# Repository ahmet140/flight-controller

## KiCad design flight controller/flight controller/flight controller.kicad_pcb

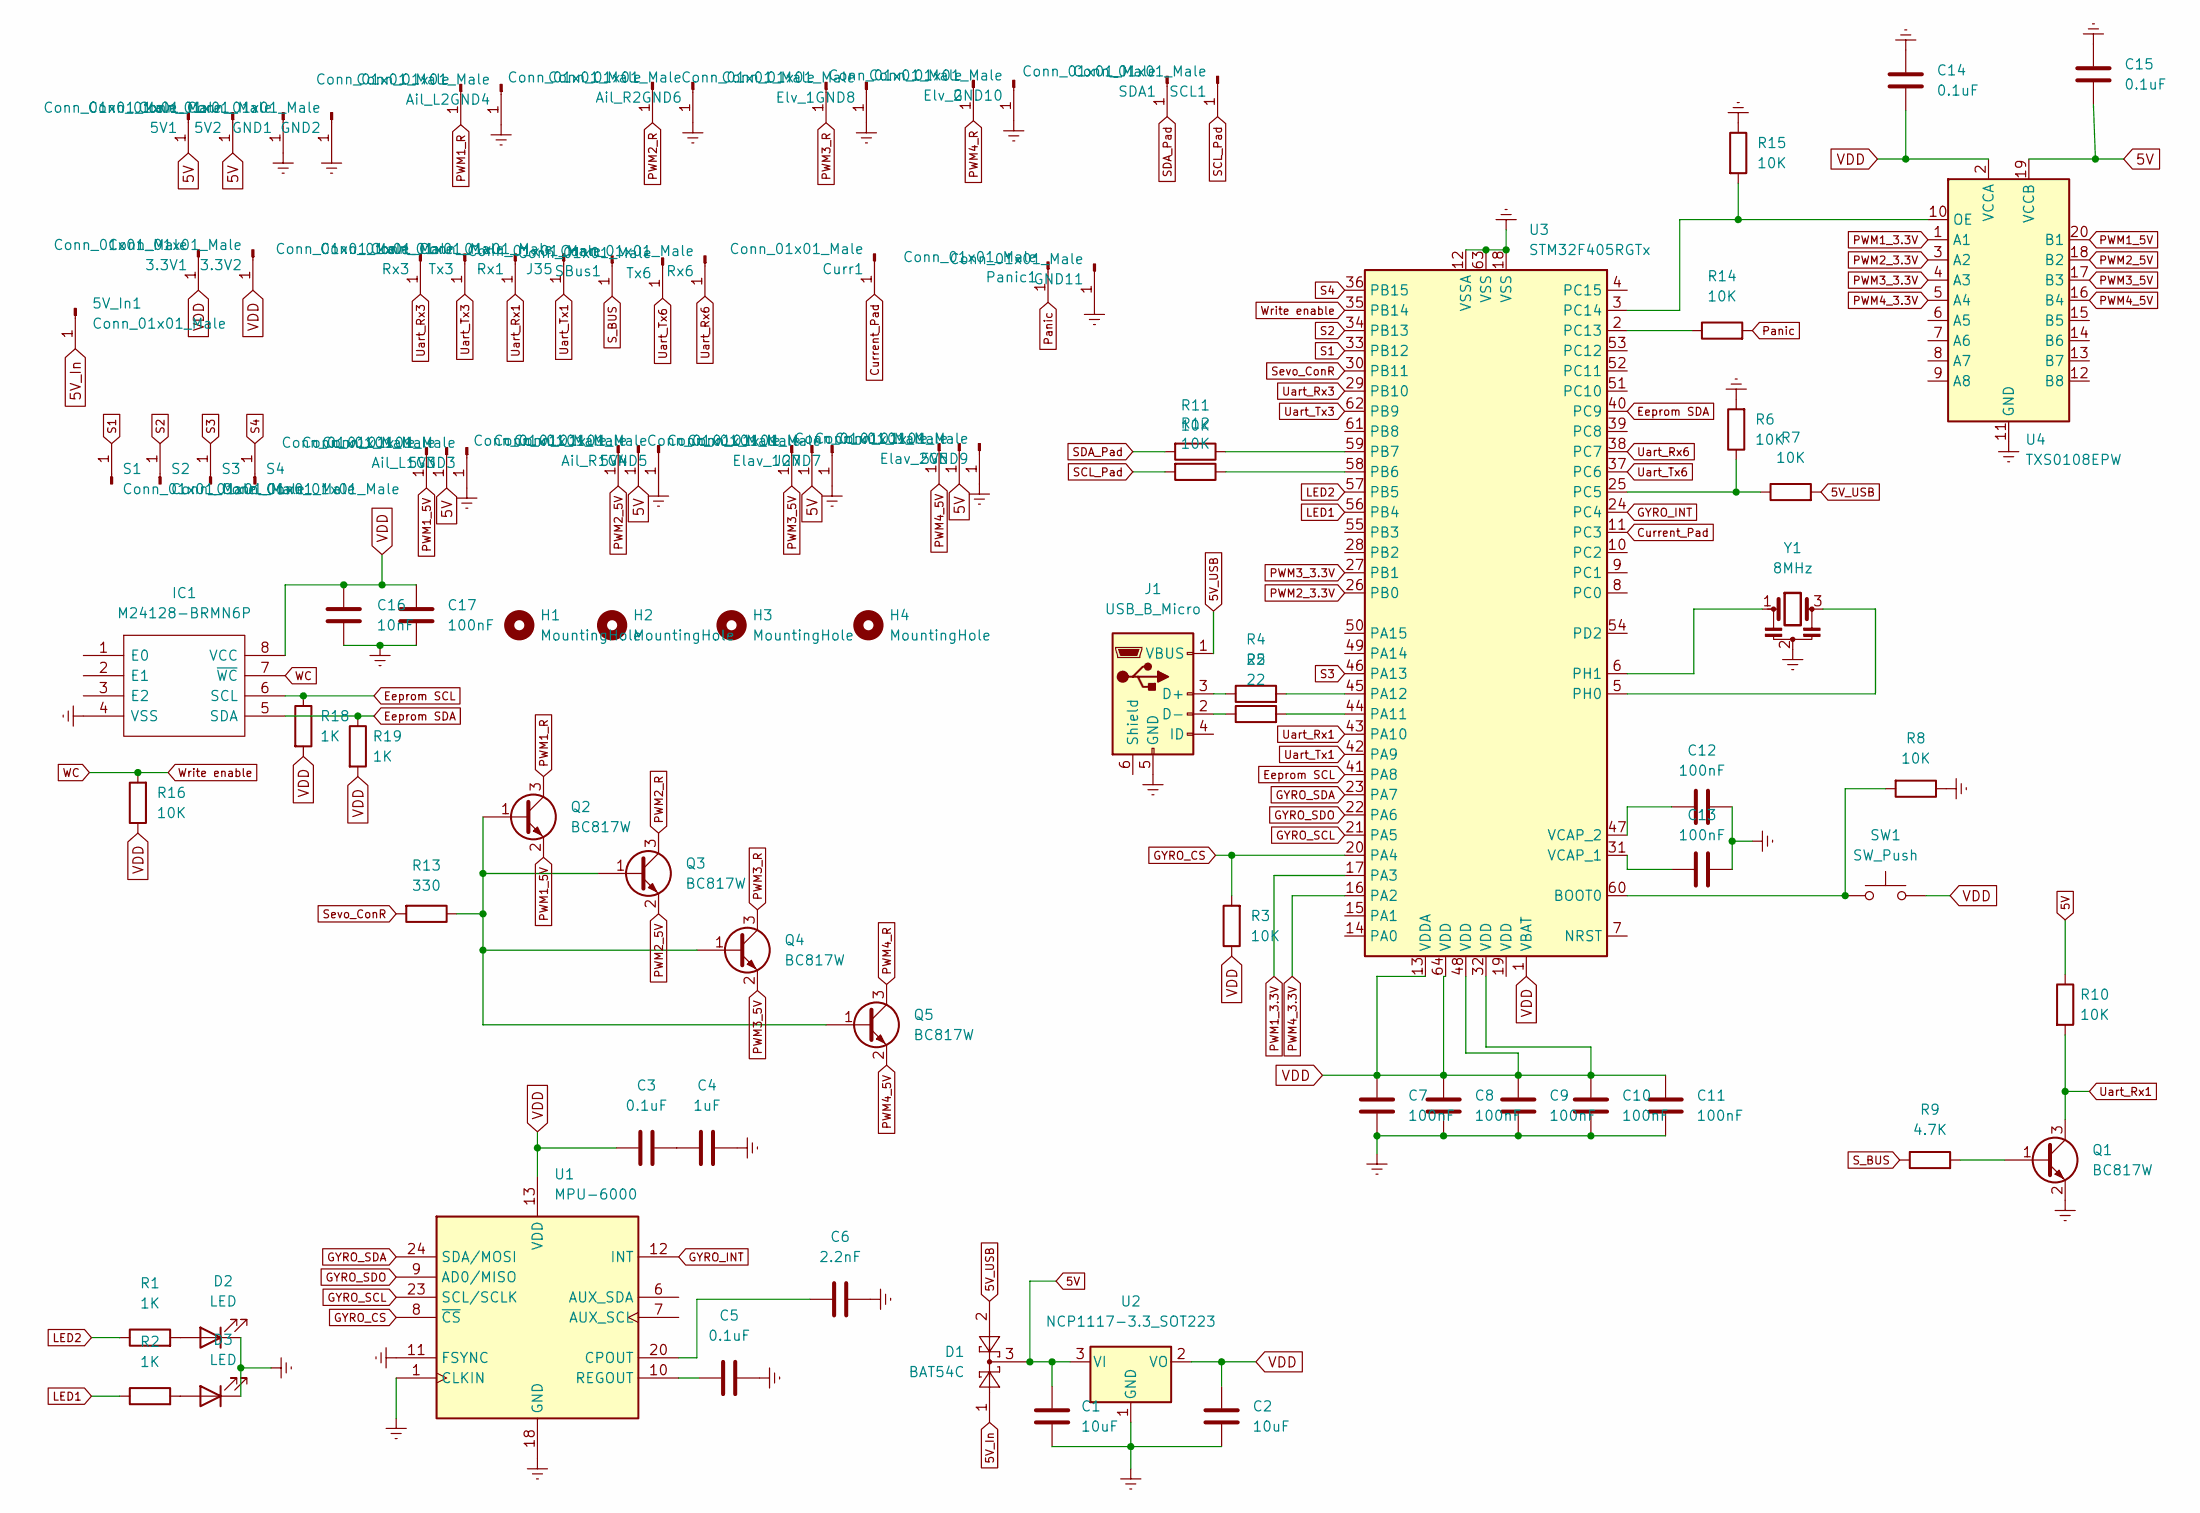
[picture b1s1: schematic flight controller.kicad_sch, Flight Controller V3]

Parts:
3.3V1, 3.3V2, 5V1, 5V2, 5V3, 5V4, 5V5, 5V_In1: Conn_01x01_Male; SolderWirePad_1x01_SMD_2x3.5mm
Ail_L1, Ail_L2: Conn_01x01_Male; SolderWirePad_1x01_SMD_2x3.5mm
Ail_R1, Ail_R2: Conn_01x01_Male; SolderWirePad_1x01_SMD_2x3.5mm
C1, C2: 10uF; C_0402_1005Metric_Pad0.74x0.62mm_HandSolder
C3, C5, C14, C15: 0.1uF; C_0402_1005Metric_Pad0.74x0.62mm_HandSolder
C4: 1uF; C_0402_1005Metric_Pad0.74x0.62mm_HandSolder
C6: 2.2nF; C_0402_1005Metric_Pad0.74x0.62mm_HandSolder
C7, C8, C9, C10, C11, C12, C13, C17: 100nF; C_0402_1005Metric_Pad0.74x0.62mm_HandSolder
C16: 10nF; C_0402_1005Metric_Pad0.74x0.62mm_HandSolder
Curr1: Conn_01x01_Male; SolderWirePad_1x01_SMD_2x3.5mm
D1: BAT54C; SOT-23
D2, D3: LED; LED_0805_2012Metric_Pad1.15x1.40mm_HandSolder
Elav_1, Elav_2: Conn_01x01_Male; SolderWirePad_1x01_SMD_2x3.5mm
Elv_1, Elv_2: Conn_01x01_Male; SolderWirePad_1x01_SMD_2x3.5mm
GND1, GND2, GND3, GND4, GND5, GND6, GND7, GND8, GND9, GND10, GND11: Conn_01x01_Male; SolderWirePad_1x01_SMD_2x3.5mm
H1, H2, H3, H4: MountingHole; MountingHole_3.2mm_M3
IC1: M24128-BRMN6P; SO-8_3.9x4.9mm_P1.27mm; Manufacturer_Part_Number M24128-BRMN6P; Mouser Part Number 511-M24128-BRMN6P
J1: USB_B_Micro; USB_Micro-B_Molex-105017-0001
J27, J35: Conn_01x01_Male; SolderWirePad_1x01_SMD_2x3.5mm
Panic1: Conn_01x01_Male; SolderWirePad_1x01_SMD_2x3.5mm
Q1, Q2, Q3, Q4, Q5: BC817W; SOT-323_SC-70
R1, R2, R18, R19: 1K; R_0402_1005Metric_Pad0.72x0.64mm_HandSolder
R3, R6, R7, R8, R10, R11, R12, R14, R15, R16: 10K; R_0402_1005Metric_Pad0.72x0.64mm_HandSolder
R4, R5: 22; R_0402_1005Metric_Pad0.72x0.64mm_HandSolder
R9: 4.7K; R_0402_1005Metric_Pad0.72x0.64mm_HandSolder
R13: 330; R_0402_1005Metric_Pad0.72x0.64mm_HandSolder
Rx1, Rx3, Rx6: Conn_01x01_Male; SolderWirePad_1x01_SMD_2x3.5mm
S1, S2, S3, S4: Conn_01x01_Male; SolderWirePad_1x01_SMD_2x3.5mm
SBus1: Conn_01x01_Male; SolderWirePad_1x01_SMD_2x3.5mm
SCL1: Conn_01x01_Male; SolderWirePad_1x01_SMD_2x3.5mm
SDA1: Conn_01x01_Male; SolderWirePad_1x01_SMD_2x3.5mm
SW1: SW_Push; SW_Push_1P1T_NO_Vertical_Wuerth_434133025816
Tx3, Tx6: Conn_01x01_Male; SolderWirePad_1x01_SMD_2x3.5mm
U1: MPU-6000; InvenSense_QFN-24_4x4mm_P0.5mm
U2: NCP1117-3.3_SOT223; SOT-223-3_TabPin2
U3: STM32F405RGTx; LQFP-64_10x10mm_P0.5mm
U4: TXS0108EPW; TSSOP-20_4.4x6.5mm_P0.65mm
Y1: 8MHz; Resonator_SMD_Murata_SFSKA-3Pin_7.9x3.8mm_HandSoldering

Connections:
5V: 5V1.1, 5V2.1, 5V3.1, 5V4.1, 5V5.1, C1.2, C15.1, D1.3, J27.1, R10.1, U2.3 (VI), U4.19 (VCCB); also elsewhere on the board
5V_In: 5V_In1.1, D1.1
5V_USB: D1.2, J1.1 (VBUS), R7.2
Current_Pad: Curr1.1, U3.11 (PC3)
Earth: C1.1, C2.1, C4.2, C5.2, C6.2, C7.1, C8.1, C9.1, C10.1, C11.1, C12.1, C13.1, C14.2, C15.2, C16.2, C17.1, D2.1 (K), D3.1 (K), GND1.1, GND2.1, GND3.1, GND4.1, GND5.1, GND6.1, GND7.1, GND8.1, GND9.1, GND10.1, GND11.1, IC1.4 (VSS), J1.5 (GND), Q1.2 (E), R6.2, R8.1, R15.1, U1.1 (CLKIN), U1.11 (FSYNC), U1.18 (GND), U2.1 (GND), U3.12 (VSSA), U3.18 (VSS), U3.63 (VSS), U4.11 (GND), Y1.2; also elsewhere on the board
Eeprom SCL: IC1.6 (SCL), R18.1, U3.41 (PA8)
Eeprom SDA: IC1.5 (SDA), R19.1, U3.40 (PC9)
GYRO_CS: R3.2, U1.8 (~CS), U3.20 (PA4)
GYRO_INT: U1.12 (INT), U3.24 (PC4)
GYRO_SCL: U1.23 (SCL/SCLK), U3.21 (PA5)
GYRO_SDA: U1.24 (SDA/MOSI), U3.23 (PA7)
GYRO_SDO: U1.9 (AD0/MISO), U3.22 (PA6)
LED1: R2.1, U3.56 (PB4)
LED2: R1.1, U3.57 (PB5)
unnamed: C3.2, C4.1
unnamed: C5.1, U1.10 (REGOUT)
unnamed: C6.1, U1.20 (CPOUT)
unnamed: C12.2, U3.47 (VCAP_2)
unnamed: C13.2, U3.31 (VCAP_1)
unnamed: D2.2 (A), R1.2
unnamed: D3.2 (A), R2.2
unnamed: J1.2 (D-), R5.1
unnamed: J1.3 (D+), R4.1
unnamed: Q1.1 (B), R9.2
unnamed: Q2.1 (B), Q3.1 (B), Q4.1 (B), Q5.1 (B), R13.1
unnamed: R4.2, U3.45 (PA12)
unnamed: R5.2, U3.44 (PA11)
unnamed: R6.1, R7.1, U3.25 (PC5)
unnamed: R8.2, SW1.1, U3.60 (BOOT0)
unnamed: R11.1, U3.59 (PB7)
unnamed: R12.1, U3.58 (PB6)
unnamed: R14.1, U3.2 (PC13)
unnamed: R15.2, U3.3 (PC14), U4.10 (OE)
unnamed: U3.5 (PH0), Y1.3
unnamed: U3.6 (PH1), Y1.1
PWM1_3.3V: U3.17 (PA3), U4.1 (A1)
PWM1_5V: Ail_L1.1, Q2.2 (E), U4.20 (B1)
PWM1_R: Ail_L2.1, Q2.3 (C)
PWM2_3.3V: U3.26 (PB0), U4.3 (A2)
PWM2_5V: Ail_R1.1, Q3.2 (E), U4.18 (B2)
PWM2_R: Ail_R2.1, Q3.3 (C)
PWM3_3.3V: U3.27 (PB1), U4.4 (A3)
PWM3_5V: Elav_1.1, Q4.2 (E), U4.17 (B3)
PWM3_R: Elv_1.1, Q4.3 (C)
PWM4_3.3V: U3.16 (PA2), U4.5 (A4)
PWM4_5V: Elav_2.1, Q5.2 (E), U4.16 (B4)
PWM4_R: Elv_2.1, Q5.3 (C)
Panic: Panic1.1, R14.2
S1: S1.1, U3.33 (PB12)
S2: S2.1, U3.34 (PB13)
S3: S3.1, U3.46 (PA13)
S4: S4.1, U3.36 (PB15)
SCL_Pad: R12.2, SCL1.1
SDA_Pad: R11.2, SDA1.1
S_BUS: R9.1, SBus1.1
Sevo_ConR: R13.2, U3.30 (PB11)
Uart_Rx1: Q1.3 (C), R10.2, Rx1.1, U3.43 (PA10)
Uart_Rx3: Rx3.1, U3.29 (PB10)
Uart_Rx6: Rx6.1, U3.38 (PC7)
Uart_Tx1: J35.1, U3.42 (PA9)
Uart_Tx3: Tx3.1, U3.62 (PB9)
Uart_Tx6: Tx6.1, U3.37 (PC6)
VDD: 3.3V1.1, 3.3V2.1, C2.2, C3.1, C7.2, C8.2, C9.2, C10.2, C11.2, C14.1, C16.1, C17.2, IC1.8 (VCC), R3.1, R16.1, R18.2, R19.2, SW1.2, U1.13 (VDD), U2.2 (VO), U3.1 (VBAT), U3.13 (VDDA), U3.32 (VDD), U3.48 (VDD), U3.64 (VDD), U4.2 (VCCA)
WC: IC1.7 (~WC), R16.2, U3.35 (PB14)

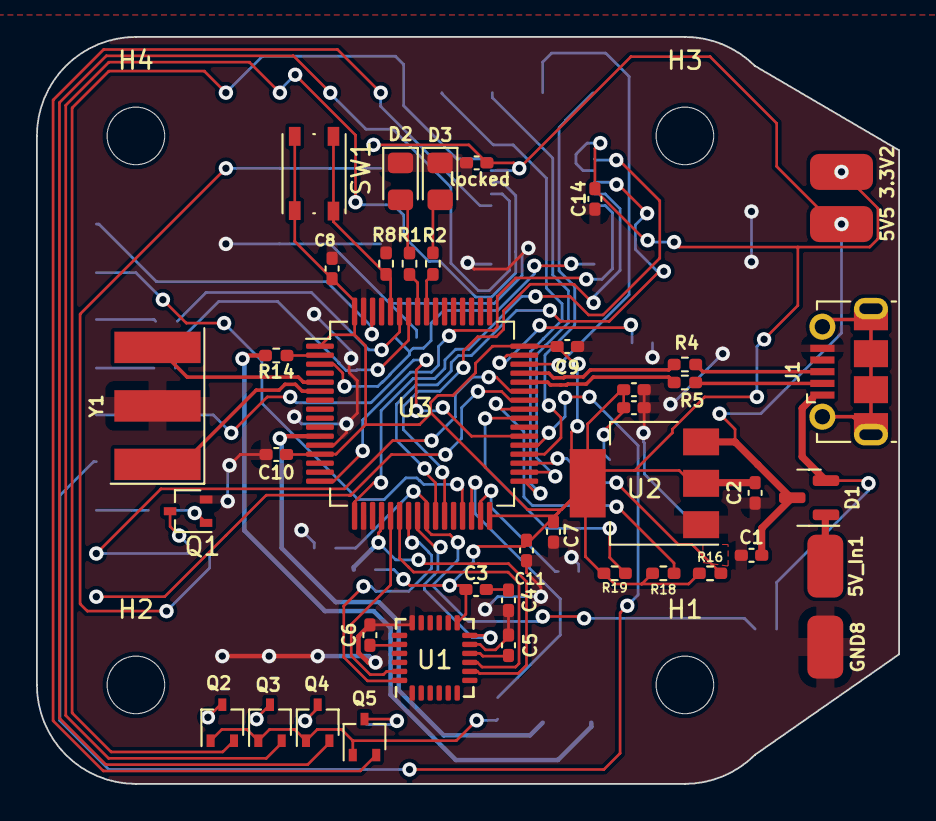
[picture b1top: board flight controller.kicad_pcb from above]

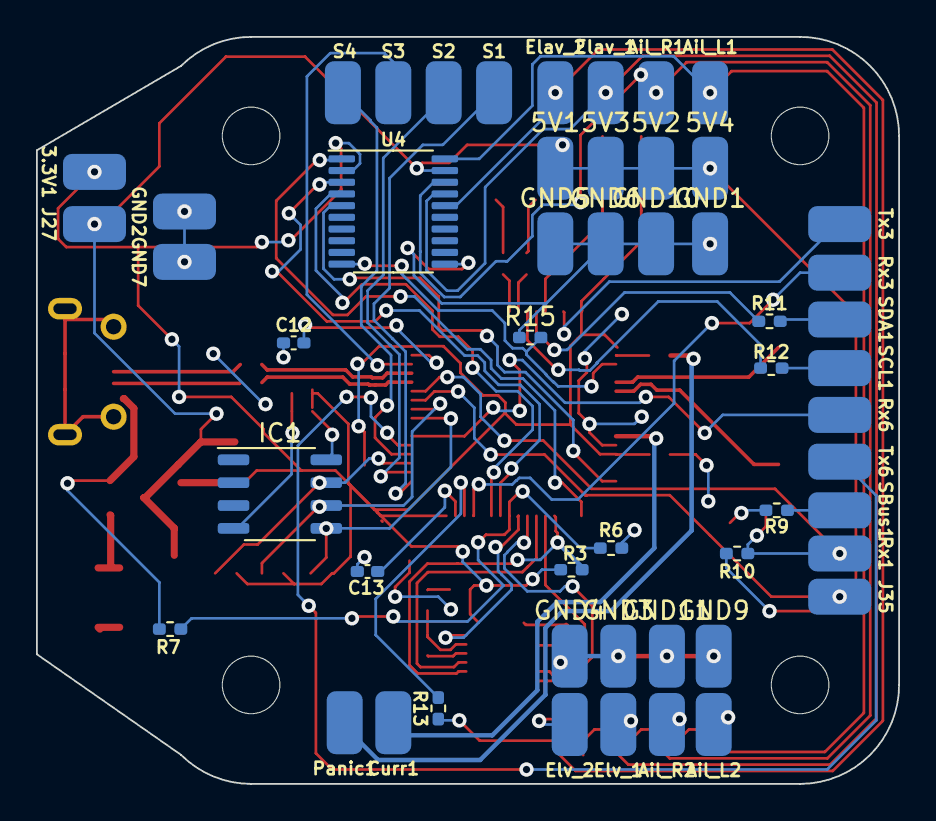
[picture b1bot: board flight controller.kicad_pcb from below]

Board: 2 copper layers, 47.9 x 41.5 mm, 98 parts (52 on the bottom side), 64 nets.

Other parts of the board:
locked: 0.1uF; C_0402_1005Metric_Pad0.74x0.62mm_HandSolder

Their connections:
5V: locked.1; also elsewhere on the board
Earth: locked.2; also elsewhere on the board

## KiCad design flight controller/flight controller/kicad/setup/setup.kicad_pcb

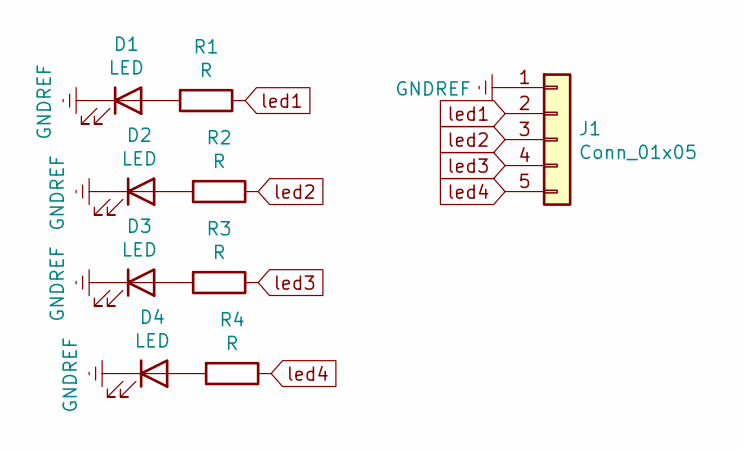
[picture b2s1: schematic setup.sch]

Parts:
D1, D2, D3, D4: LED; LED_D3.0mm
J1: Conn_01x05; PinHeader_1x05_P2.54mm_Horizontal
R1, R2, R3, R4: R; R_Axial_DIN0204_L3.6mm_D1.6mm_P5.08mm_Horizontal

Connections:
GNDREF: D1.1 (K), D2.1 (K), D3.1 (K), D4.1 (K), J1.1
unnamed: D1.2 (A), R1.2
unnamed: D2.2 (A), R2.2
unnamed: D3.2 (A), R3.2
unnamed: D4.2 (A), R4.2
led1: J1.2, R1.1
led2: J1.3, R2.1
led3: J1.4, R3.1
led4: J1.5, R4.1

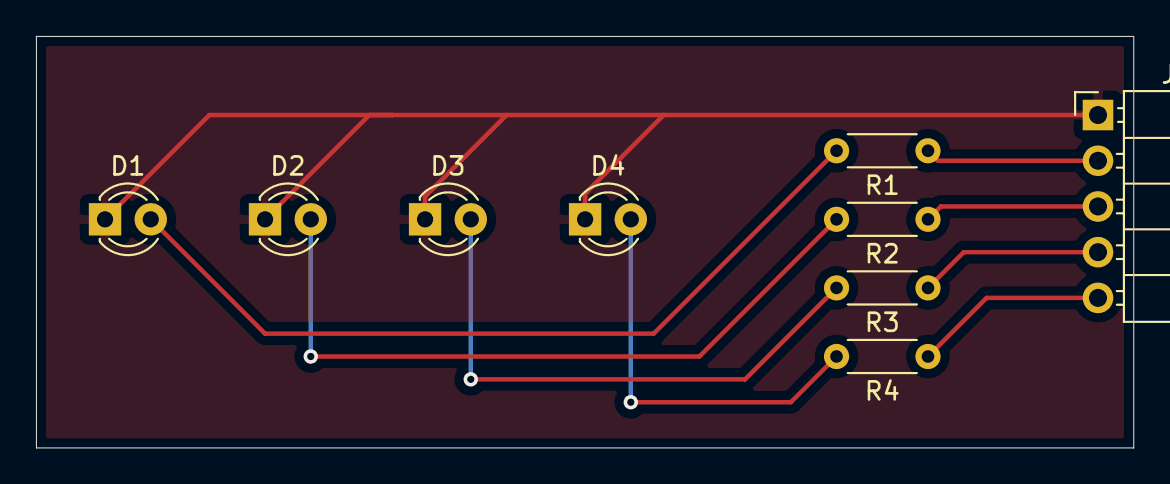
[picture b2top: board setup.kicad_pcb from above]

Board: 2 copper layers, 61.0 x 22.9 mm, 9 parts (0 on the bottom side), 9 nets.

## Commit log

2024-01-05 corrected unconnected pad error and updated files to new version
